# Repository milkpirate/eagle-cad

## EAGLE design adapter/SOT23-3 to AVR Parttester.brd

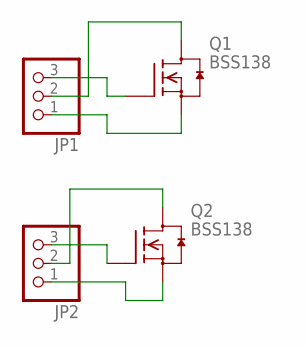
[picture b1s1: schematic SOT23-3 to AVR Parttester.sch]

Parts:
JP1, JP2: PINHD-1X3; 1X03
Q1, Q2: BSS138; SOT23

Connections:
1: JP1.3, Q1.1 (G)
2: JP1.2, Q1.3 (D)
3: JP1.1, Q1.2 (S)
11: JP2.3, Q2.1 (G)
22: JP2.2, Q2.3 (D)
33: JP2.1, Q2.2 (S)

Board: 2 copper layers, 4 parts (0 on the bottom side), 6 nets, no tracks yet.

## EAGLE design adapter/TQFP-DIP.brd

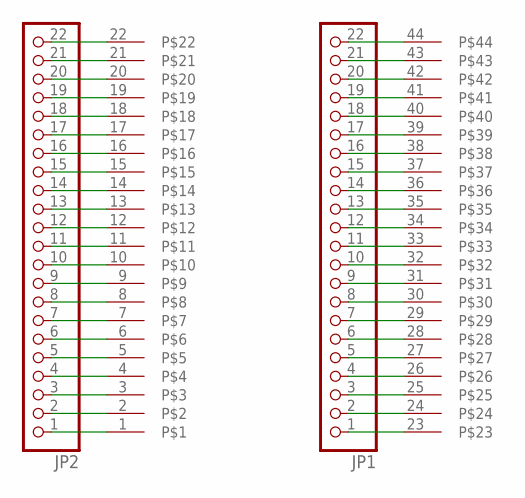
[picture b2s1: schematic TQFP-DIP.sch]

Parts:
JP1, JP2: PINHD-1X22; 1X22
U$1: TQFP44

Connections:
unnamed: JP2.1, U$1.1
unnamed: JP2.2, U$1.2
unnamed: JP2.3, U$1.3
unnamed: JP2.4, U$1.4
unnamed: JP2.5, U$1.5
unnamed: JP2.6, U$1.6
unnamed: JP2.7, U$1.7
unnamed: JP2.8, U$1.8
unnamed: JP2.9, U$1.9
unnamed: JP2.10, U$1.10
unnamed: JP2.11, U$1.11
unnamed: JP2.12, U$1.12
unnamed: JP2.13, U$1.13
unnamed: JP2.14, U$1.14
unnamed: JP2.15, U$1.15
unnamed: JP2.16, U$1.16
unnamed: JP2.17, U$1.17
unnamed: JP2.18, U$1.18
unnamed: JP2.19, U$1.19
unnamed: JP2.20, U$1.20
unnamed: JP2.21, U$1.21
unnamed: JP2.22, U$1.22
unnamed: JP1.1, U$1.23
unnamed: JP1.2, U$1.24
unnamed: JP1.3, U$1.25
unnamed: JP1.4, U$1.26
unnamed: JP1.5, U$1.27
unnamed: JP1.6, U$1.28
unnamed: JP1.7, U$1.29
unnamed: JP1.8, U$1.30
unnamed: JP1.9, U$1.31
unnamed: JP1.10, U$1.32
unnamed: JP1.11, U$1.33
unnamed: JP1.12, U$1.34
unnamed: JP1.13, U$1.35
unnamed: JP1.14, U$1.36
unnamed: JP1.15, U$1.37
unnamed: JP1.16, U$1.38
unnamed: JP1.17, U$1.39
unnamed: JP1.18, U$1.40
unnamed: JP1.19, U$1.41
unnamed: JP1.20, U$1.42
unnamed: JP1.21, U$1.43
unnamed: JP1.22, U$1.44

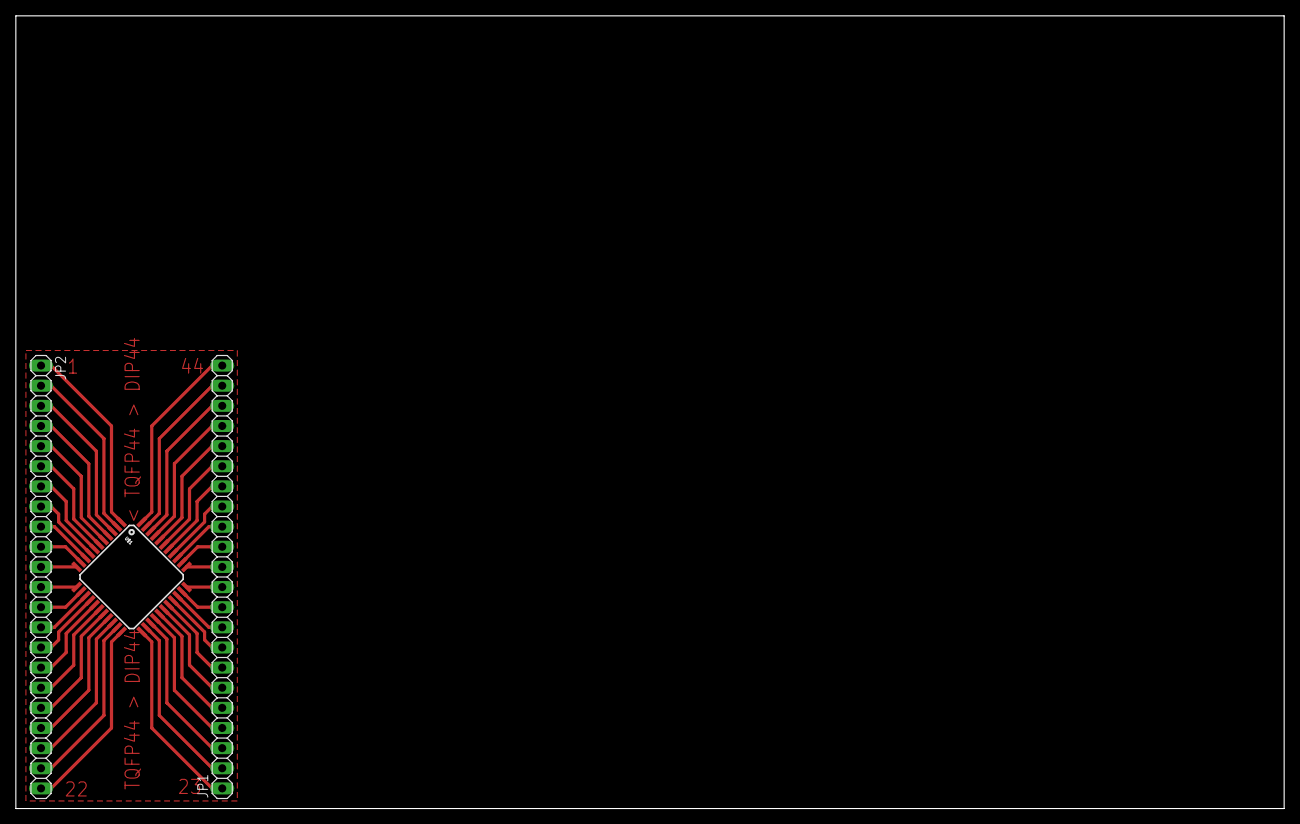
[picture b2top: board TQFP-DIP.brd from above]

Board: 2 copper layers, 160.0 x 100.0 mm, 3 parts (0 on the bottom side), 44 nets.

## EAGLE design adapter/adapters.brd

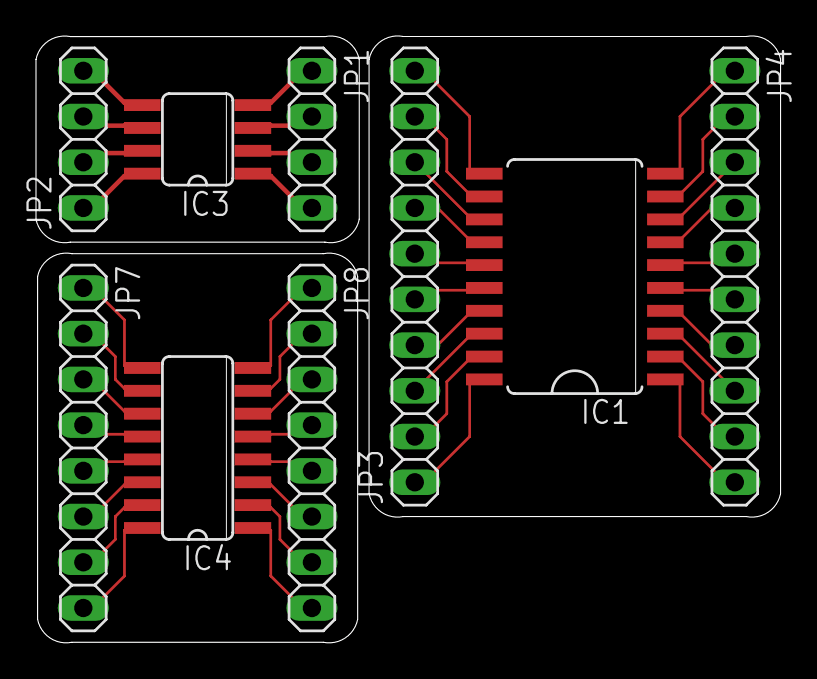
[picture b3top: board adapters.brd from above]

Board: 2 copper layers, 41.4 x 33.7 mm, 9 parts (0 on the bottom side), 44 nets.

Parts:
IC1: 74HCT573D; SO20W
IC3: MAX366CSA; SO08
IC4: MAX3232CSE; SO16
JP1, JP2: 1X04
JP3, JP4: 1X10
JP7, JP8: 1X08

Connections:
unnamed: IC3.1, JP1.4
unnamed: IC3.2, JP1.3
unnamed: IC3.3, JP1.2
unnamed: IC3.4, JP1.1
unnamed: IC3.5, JP2.4
unnamed: IC3.6, JP2.3
unnamed: IC3.7, JP2.2
unnamed: IC3.8, JP2.1
unnamed: IC4.1, JP8.8
unnamed: IC4.3, JP8.6
unnamed: IC4.2, JP8.7
unnamed: IC4.4, JP8.5
unnamed: IC4.5, JP8.4
unnamed: IC4.6, JP8.3
unnamed: IC4.7, JP8.2
unnamed: IC4.8, JP8.1
unnamed: IC4.16, JP7.8
unnamed: IC4.15, JP7.7
unnamed: IC4.14, JP7.6
unnamed: IC4.13, JP7.5
unnamed: IC4.12, JP7.4
unnamed: IC4.11, JP7.3
unnamed: IC4.10, JP7.2
unnamed: IC4.9, JP7.1
unnamed: IC1.2, JP4.9
unnamed: IC1.3, JP4.8
unnamed: IC1.4, JP4.7
unnamed: IC1.5, JP4.6
unnamed: IC1.6, JP4.5
unnamed: IC1.7, JP4.4
unnamed: IC1.8, JP4.3
unnamed: IC1.9, JP4.2
unnamed: IC1.10, JP4.1
unnamed: IC1.1, JP4.10
unnamed: IC1.11, JP3.10
unnamed: IC1.12, JP3.9
unnamed: IC1.13, JP3.8
unnamed: IC1.14, JP3.7
unnamed: IC1.15, JP3.6
unnamed: IC1.16, JP3.5
unnamed: IC1.17, JP3.4
unnamed: IC1.18, JP3.3
unnamed: IC1.19, JP3.2
unnamed: IC1.20, JP3.1

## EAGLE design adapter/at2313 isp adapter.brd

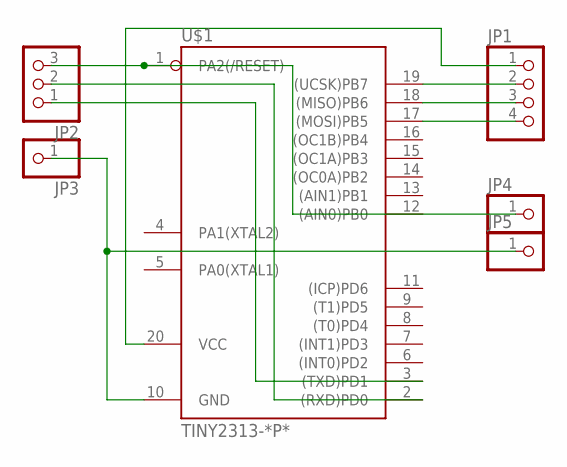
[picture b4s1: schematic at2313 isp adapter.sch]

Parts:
JP1: PINHD-1X4; 1X04
JP2: PINHD-1X3; 1X03
JP3, JP4, JP5: PINHD-1X1; 1X01
U$1: TINY2313-*P*; DIL20

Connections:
GND: JP3.1, JP5.1, U$1.10 (GND)
unnamed: JP1.2, U$1.19 ((UCSK)PB7)
unnamed: JP1.3, U$1.18 ((MISO)PB6)
unnamed: JP1.4, U$1.17 ((MOSI)PB5)
unnamed: JP1.1, U$1.20 (VCC)
unnamed: JP2.3, JP4.1, U$1.1 (PA2(/RESET))
unnamed: JP2.2, U$1.2 ((RXD)PD0)
unnamed: JP2.1, U$1.3 ((TXD)PD1)

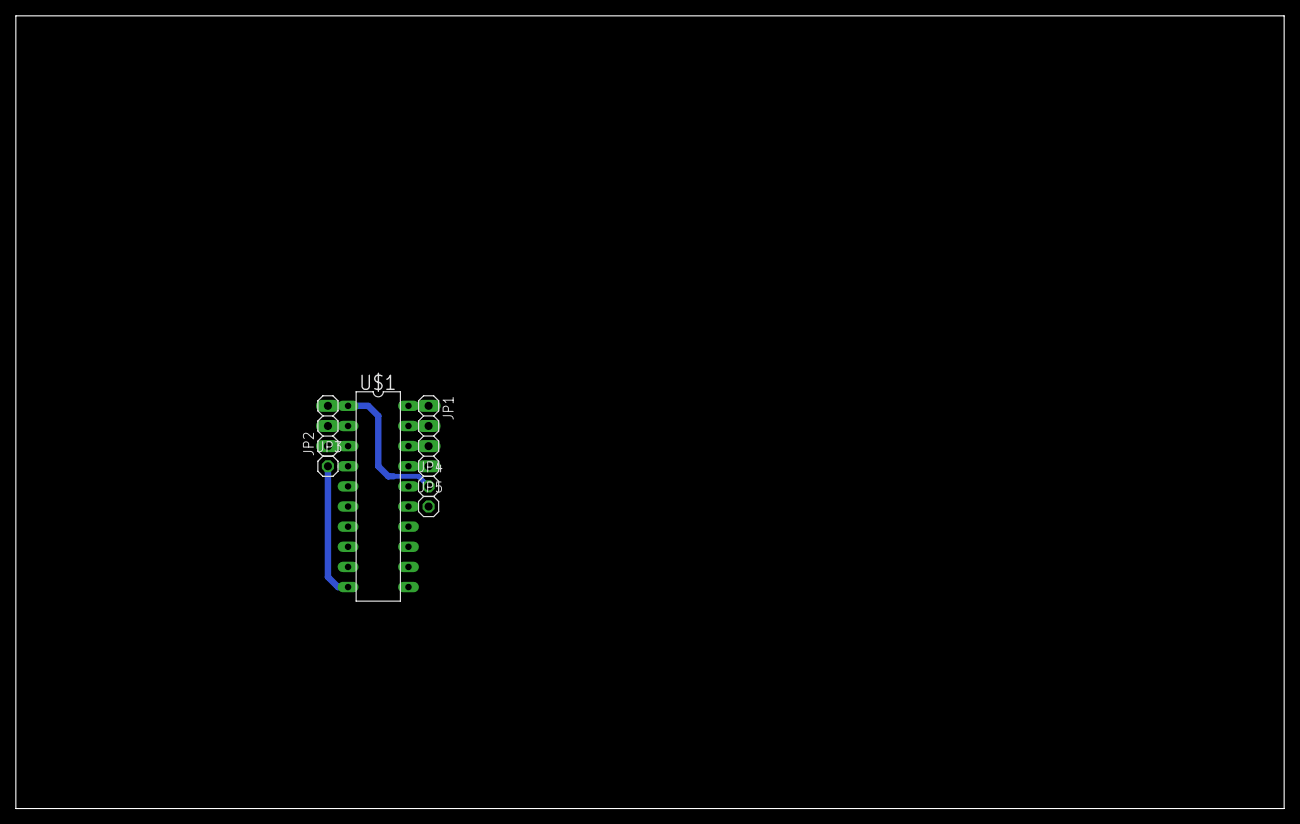
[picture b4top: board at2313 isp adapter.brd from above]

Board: 2 copper layers, 160.0 x 100.0 mm, 6 parts (0 on the bottom side), 8 nets.

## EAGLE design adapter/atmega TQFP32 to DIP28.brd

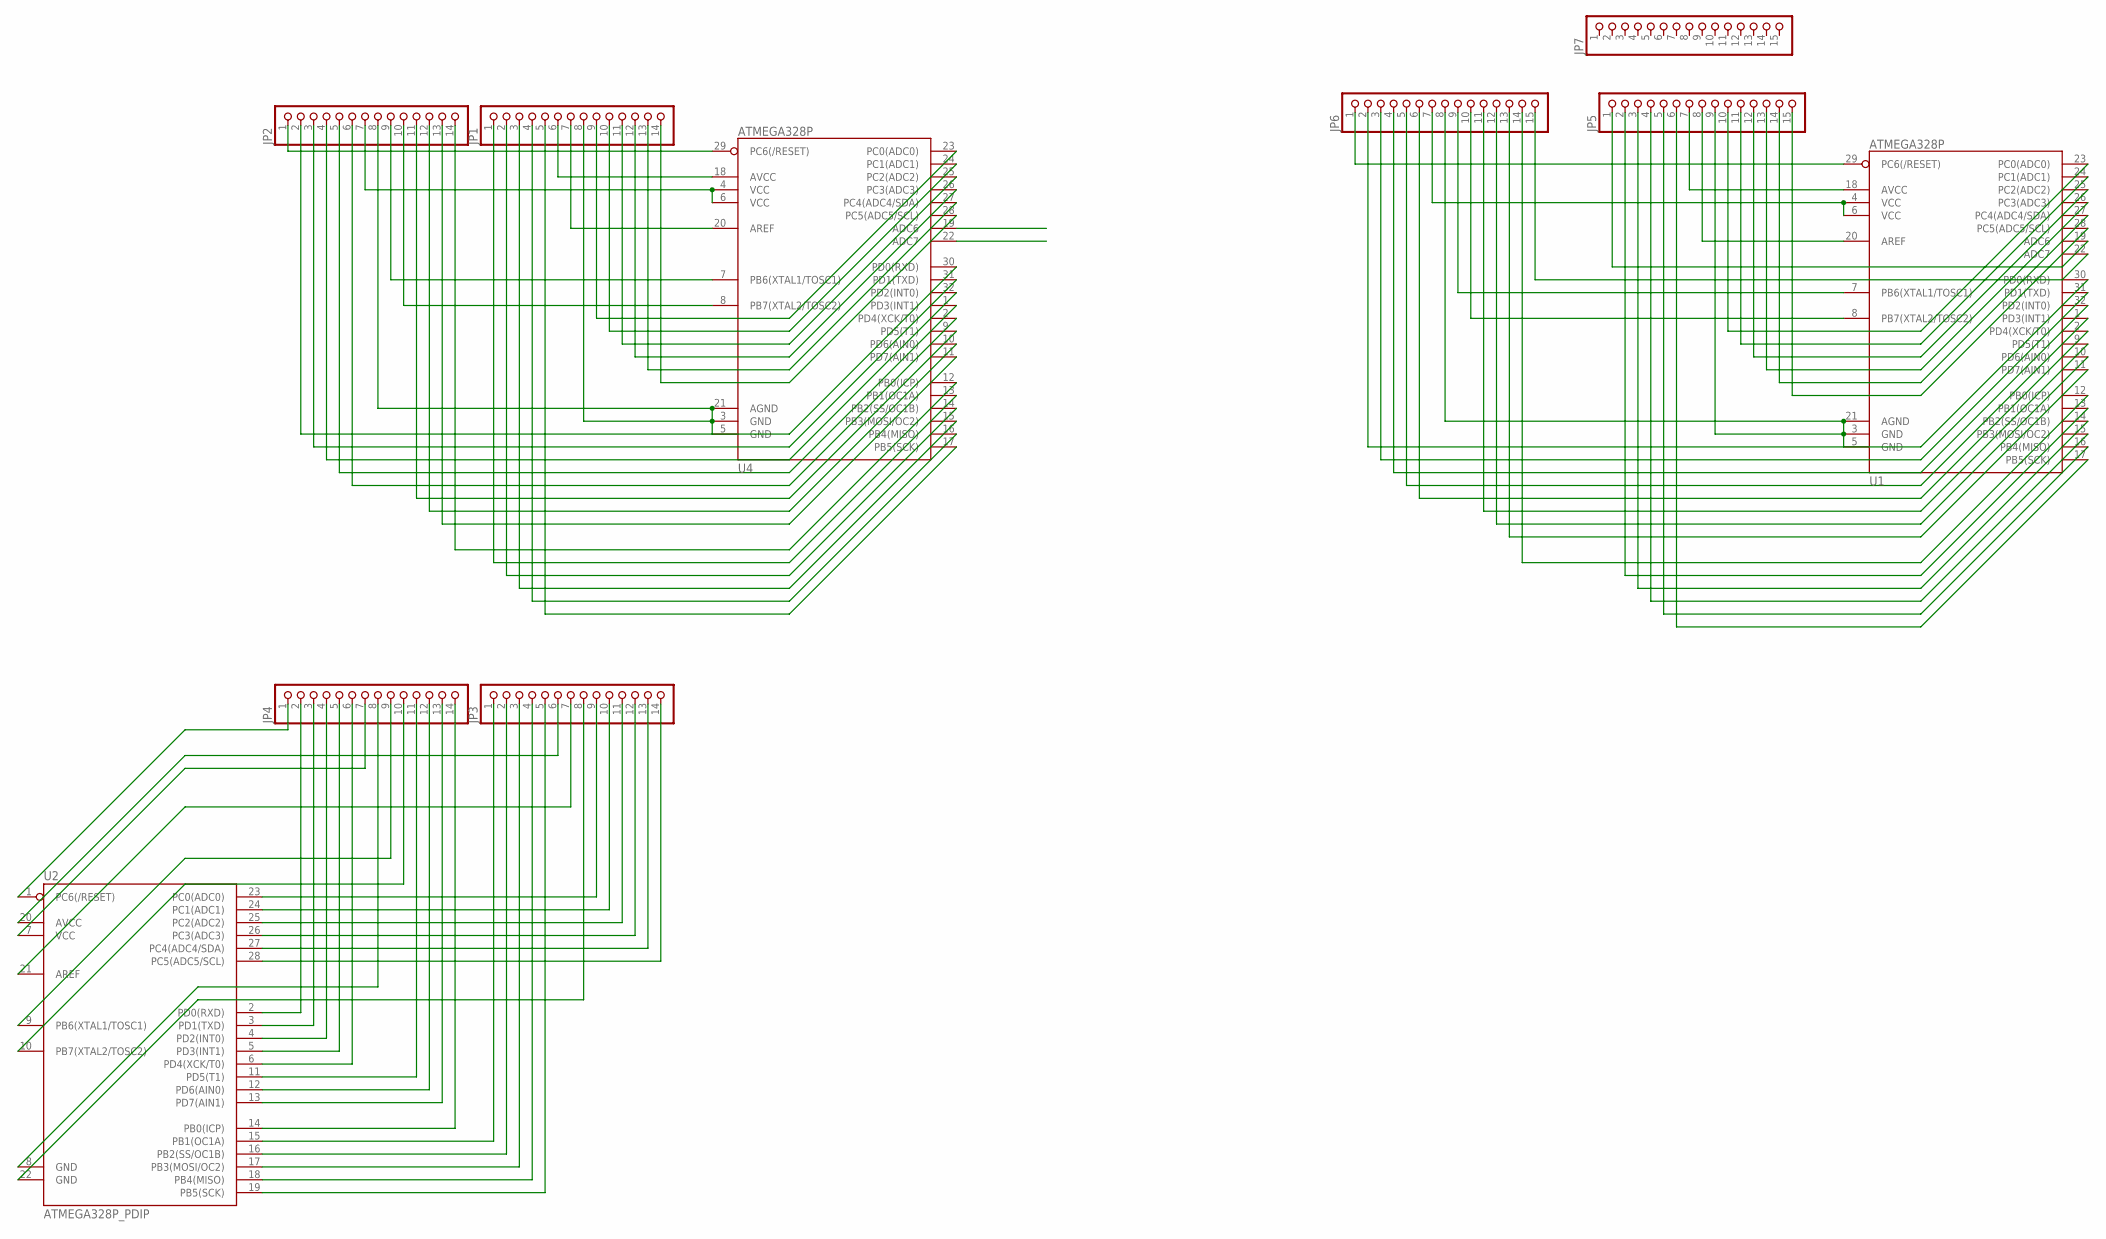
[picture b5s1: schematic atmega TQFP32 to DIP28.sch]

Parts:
JP1, JP2, JP3, JP4: PINHD-1X14; 1X14
JP5, JP6, JP7: PINHD-1X15; 1X15
U1, U4: ATMEGA328P; TQFP32-08
U2: ATMEGA328P_PDIP; DIL28-3

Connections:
GND: JP1.8, JP2.8, U4.3 (GND), U4.5 (GND), U4.21 (AGND)
GND1: JP5.9, JP6.8, U1.3 (GND), U1.5 (GND), U1.21 (AGND)
unnamed: JP2.1, U4.29 (PC6(/RESET))
unnamed: JP1.6, U4.18 (AVCC)
unnamed: JP1.7, U4.20 (AREF)
unnamed: JP2.9, U4.7 (PB6(XTAL1/TOSC1))
unnamed: JP2.10, U4.8 (PB7(XTAL2/TOSC2))
unnamed: JP4.1, U2.1 (PC6(/RESET))
unnamed: JP1.9, U4.23 (PC0(ADC0))
unnamed: JP1.10, U4.24 (PC1(ADC1))
unnamed: JP1.11, U4.25 (PC2(ADC2))
unnamed: JP1.12, U4.26 (PC3(ADC3))
unnamed: JP1.13, U4.27 (PC4(ADC4/SDA))
unnamed: JP1.14, U4.28 (PC5(ADC5/SCL))
unnamed: JP2.2, U4.30 (PD0(RXD))
unnamed: JP2.3, U4.31 (PD1(TXD))
unnamed: JP2.4, U4.32 (PD2(INT0))
unnamed: JP2.5, U4.1 (PD3(INT1))
unnamed: JP2.6, U4.2 (PD4(XCK/T0))
unnamed: JP2.11, U4.9 (PD5(T1))
unnamed: JP2.12, U4.10 (PD6(AIN0))
unnamed: JP2.13, U4.11 (PD7(AIN1))
unnamed: JP2.14, U4.12 (PB0(ICP))
unnamed: JP1.1, U4.13 (PB1(OC1A))
unnamed: JP1.2, U4.14 (PB2(SS/OC1B))
unnamed: JP1.3, U4.15 (PB3(MOSI/OC2))
unnamed: JP1.4, U4.16 (PB4(MISO))
unnamed: JP1.5, U4.17 (PB5(SCK))
unnamed: JP3.6, U2.20 (AVCC)
unnamed: JP4.7, U2.7 (VCC)
unnamed: JP3.7, U2.21 (AREF)
unnamed: JP4.9, U2.9 (PB6(XTAL1/TOSC1))
unnamed: JP4.10, U2.10 (PB7(XTAL2/TOSC2))
unnamed: JP4.8, U2.8 (GND)
unnamed: JP3.9, U2.23 (PC0(ADC0))
unnamed: JP3.10, U2.24 (PC1(ADC1))
unnamed: JP3.11, U2.25 (PC2(ADC2))
unnamed: JP3.12, U2.26 (PC3(ADC3))
unnamed: JP3.13, U2.27 (PC4(ADC4/SDA))
unnamed: JP3.14, U2.28 (PC5(ADC5/SCL))
unnamed: JP4.2, U2.2 (PD0(RXD))
unnamed: JP4.3, U2.3 (PD1(TXD))
unnamed: JP4.4, U2.4 (PD2(INT0))
unnamed: JP4.5, U2.5 (PD3(INT1))
unnamed: JP4.6, U2.6 (PD4(XCK/T0))
unnamed: JP4.11, U2.11 (PD5(T1))
unnamed: JP4.12, U2.12 (PD6(AIN0))
unnamed: JP4.13, U2.13 (PD7(AIN1))
unnamed: JP4.14, U2.14 (PB0(ICP))
unnamed: JP3.1, U2.15 (PB1(OC1A))
unnamed: JP3.2, U2.16 (PB2(SS/OC1B))
unnamed: JP3.3, U2.17 (PB3(MOSI/OC2))
unnamed: JP3.4, U2.18 (PB4(MISO))
unnamed: JP3.5, U2.19 (PB5(SCK))
unnamed: JP6.1, U1.29 (PC6(/RESET))
unnamed: JP5.7, U1.18 (AVCC)
unnamed: JP5.8, U1.20 (AREF)
unnamed: JP6.9, U1.7 (PB6(XTAL1/TOSC1))
unnamed: JP6.10, U1.8 (PB7(XTAL2/TOSC2))
unnamed: JP5.10, U1.23 (PC0(ADC0))
unnamed: JP5.11, U1.24 (PC1(ADC1))
unnamed: JP5.12, U1.25 (PC2(ADC2))
unnamed: JP5.13, U1.26 (PC3(ADC3))
unnamed: JP5.14, U1.27 (PC4(ADC4/SDA))
unnamed: JP5.15, U1.28 (PC5(ADC5/SCL))
unnamed: JP6.2, U1.30 (PD0(RXD))
unnamed: JP6.3, U1.31 (PD1(TXD))
unnamed: JP6.4, U1.32 (PD2(INT0))
unnamed: JP6.5, U1.1 (PD3(INT1))
unnamed: JP6.6, U1.2 (PD4(XCK/T0))
unnamed: JP6.11, U1.9 (PD5(T1))
unnamed: JP6.12, U1.10 (PD6(AIN0))
unnamed: JP6.13, U1.11 (PD7(AIN1))
unnamed: JP6.14, U1.12 (PB0(ICP))
unnamed: JP5.2, U1.13 (PB1(OC1A))
unnamed: JP5.3, U1.14 (PB2(SS/OC1B))
unnamed: JP5.4, U1.15 (PB3(MOSI/OC2))
unnamed: JP5.5, U1.16 (PB4(MISO))
unnamed: JP5.6, U1.17 (PB5(SCK))
unnamed: JP5.1, U1.19 (ADC6)
unnamed: JP6.15, U1.22 (ADC7)
unnamed: JP3.8, U2.22 (GND)
VCC: JP2.7, U4.4 (VCC), U4.6 (VCC)
VCC1: JP6.7, U1.4 (VCC), U1.6 (VCC)

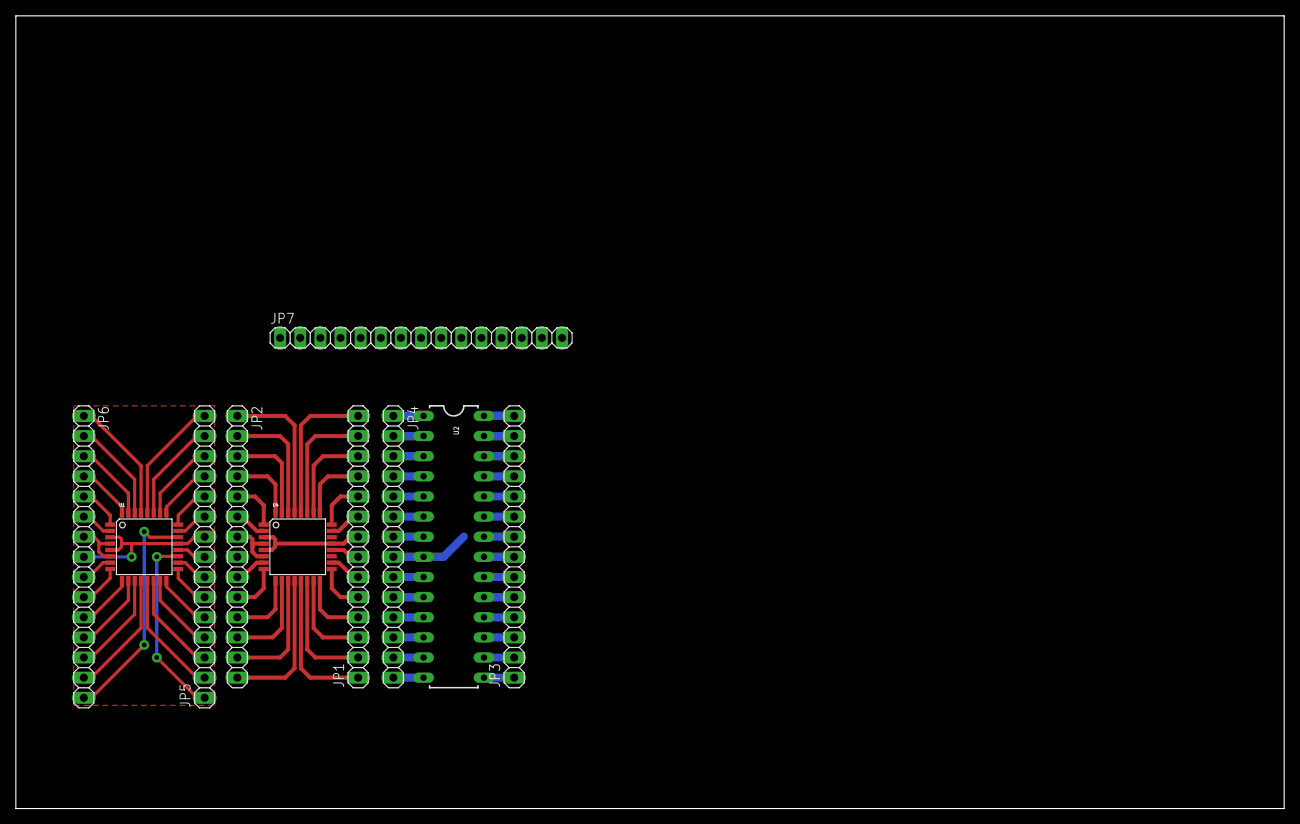
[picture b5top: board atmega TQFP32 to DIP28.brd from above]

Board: 2 copper layers, 160.0 x 100.0 mm, 10 parts (0 on the bottom side), 84 nets.

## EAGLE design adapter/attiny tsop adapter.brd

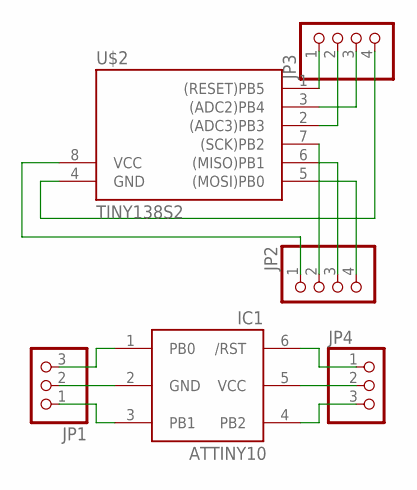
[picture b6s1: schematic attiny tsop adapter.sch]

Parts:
IC1: ATTINY10; SOT23-6
JP1, JP4: PINHD-1X3; 1X03
JP2, JP3: PINHD-1X4; 1X04
U$2: TINY138S2; SO08

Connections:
1: IC1.4 (PB2), JP4.3
2: IC1.5 (VCC), JP4.2
3: IC1.6 (/RST), JP4.1
4: IC1.1 (PB0), JP1.3
5: IC1.2 (GND), JP1.2
6: IC1.3 (PB1), JP1.1
unnamed: JP3.1, U$2.1 ((RESET)PB5)
unnamed: JP3.2, U$2.2 ((ADC3)PB3)
unnamed: JP3.3, U$2.3 ((ADC2)PB4)
unnamed: JP3.4, U$2.4 (GND)
unnamed: JP2.4, U$2.5 ((MOSI)PB0)
unnamed: JP2.3, U$2.6 ((MISO)PB1)
unnamed: JP2.2, U$2.7 ((SCK)PB2)
unnamed: JP2.1, U$2.8 (VCC)

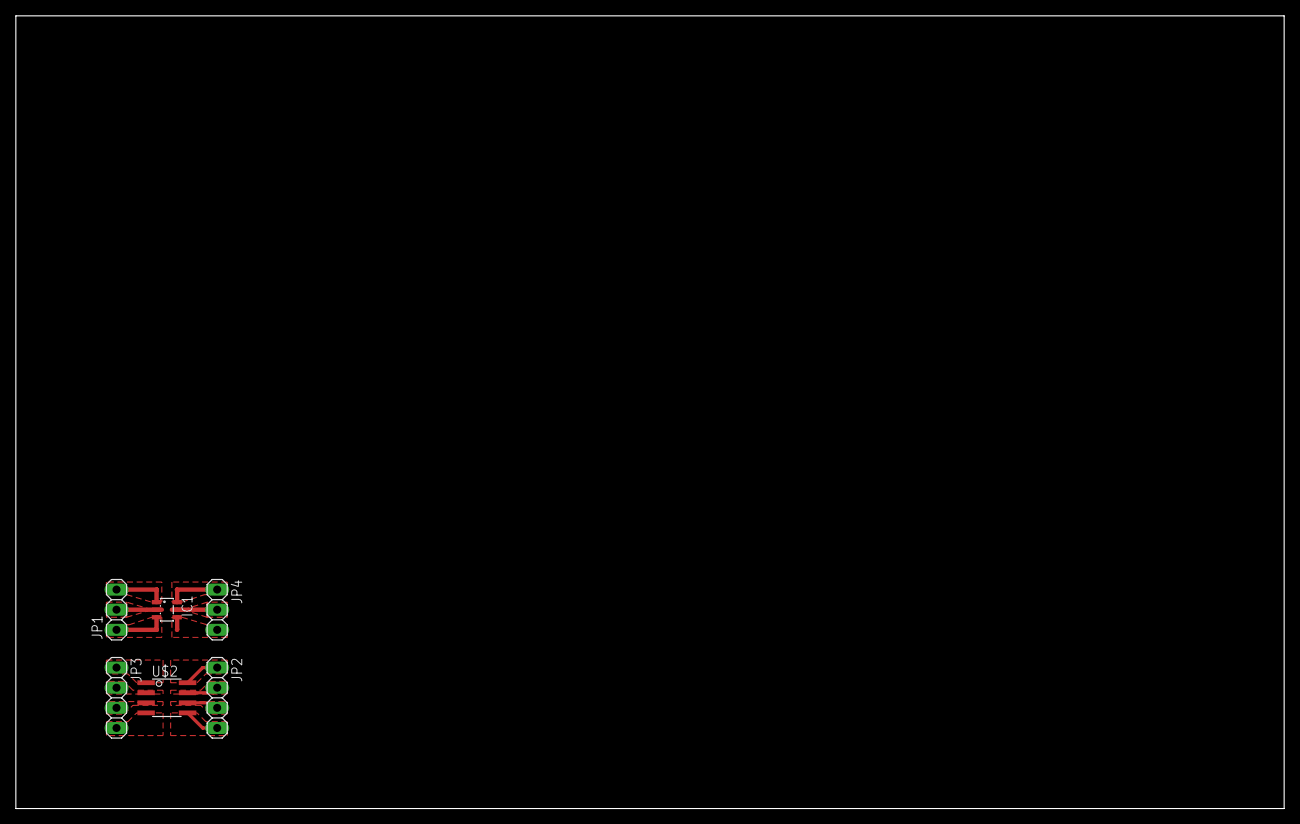
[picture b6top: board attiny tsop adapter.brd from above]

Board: 2 copper layers, 160.0 x 100.0 mm, 6 parts (0 on the bottom side), 14 nets.

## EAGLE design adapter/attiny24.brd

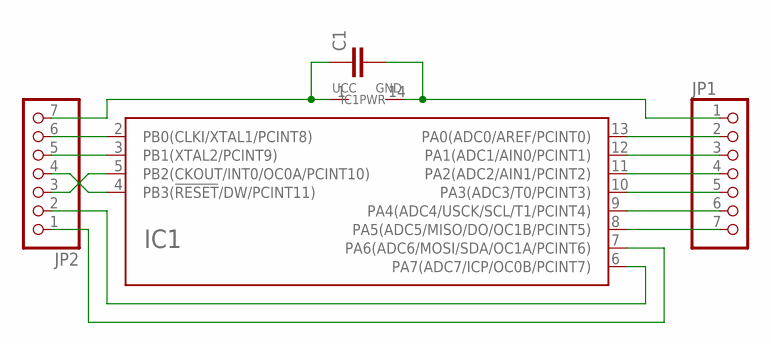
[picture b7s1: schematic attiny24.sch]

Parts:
C1: C-EUC0805K; C0805K
IC1: ATTINY24/44/84-SSU; SOIC14
JP1, JP2: PINHD-1X7; 1X07

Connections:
unnamed: C1.1, IC1.1 (UCC), JP2.7
unnamed: C1.2, IC1.14 (GND), JP1.1
unnamed: IC1.4 (PB3(!RESET!/DW/PCINT11)), JP2.4
unnamed: IC1.2 (PB0(CLKI/XTAL1/PCINT8)), JP2.6
unnamed: IC1.3 (PB1(XTAL2/PCINT9)), JP2.5
unnamed: IC1.5 (PB2(CKOUT/INT0/OC0A/PCINT10)), JP2.3
unnamed: IC1.6 (PA7(ADC7/ICP/OC0B/PCINT7)), JP2.2
unnamed: IC1.7 (PA6(ADC6/MOSI/SDA/OC1A/PCINT6)), JP2.1
unnamed: IC1.13 (PA0(ADC0/AREF/PCINT0)), JP1.2
unnamed: IC1.12 (PA1(ADC1/AIN0/PCINT1)), JP1.3
unnamed: IC1.11 (PA2(ADC2/AIN1/PCINT2)), JP1.4
unnamed: IC1.10 (PA3(ADC3/T0/PCINT3)), JP1.5
unnamed: IC1.9 (PA4(ADC4/USCK/SCL/T1/PCINT4)), JP1.6
unnamed: IC1.8 (PA5(ADC5/MISO/DO/OC1B/PCINT5)), JP1.7

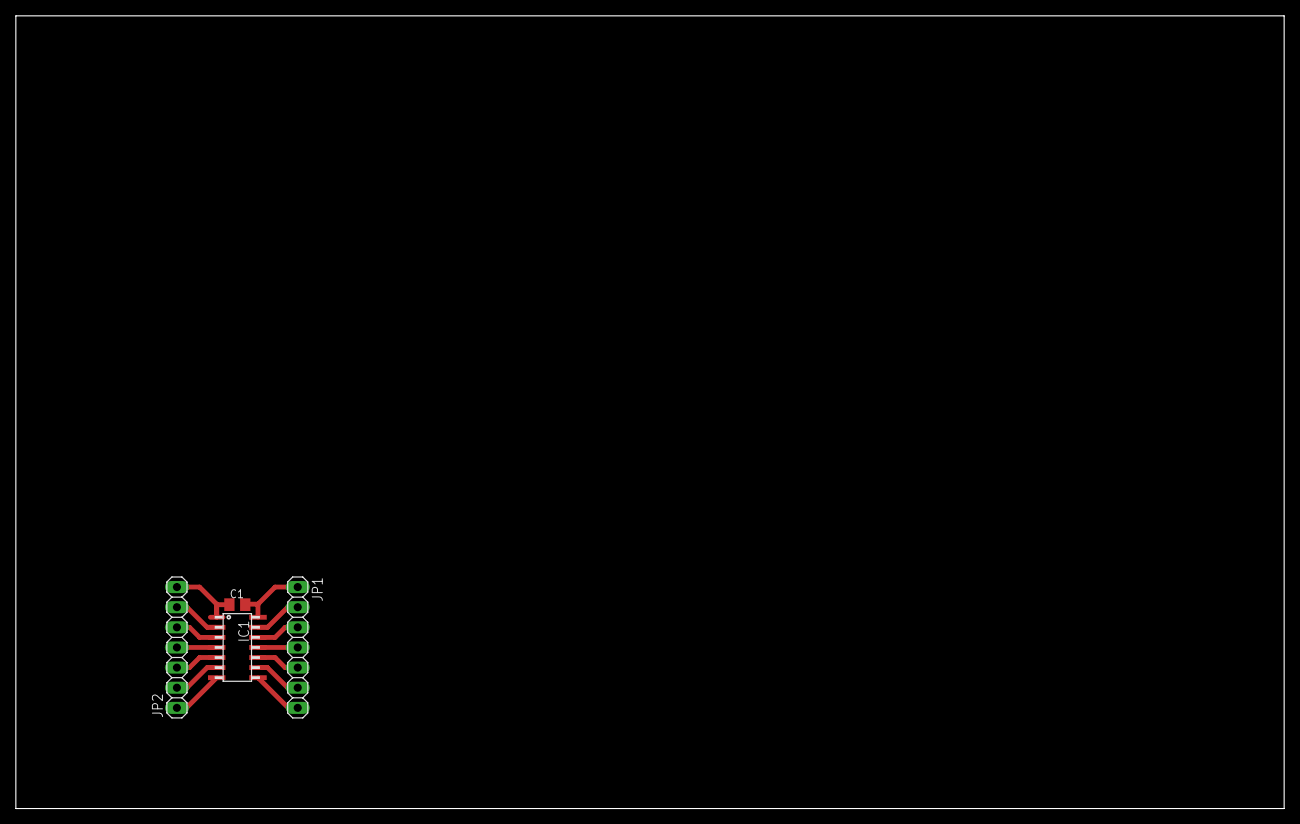
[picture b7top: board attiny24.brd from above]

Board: 2 copper layers, 160.0 x 100.0 mm, 4 parts (0 on the bottom side), 14 nets.

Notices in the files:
parts and their libraries:
m-pad-2.1: License : GNU General Public License version 2 (see bottom)
SparkFun: Licensing: CC v3.0 Share-Alike You are welcome to use this library for commercial purposes.
